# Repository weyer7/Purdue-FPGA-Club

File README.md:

# FPGA Club

Promoting student-led design, verification, and implementation of user-defined hardware.

---

## General Meeting Information
- **Meeting Frequency**: Biweekly  
- **Location**: BHEE 117 (ECE 270 Lab)  
- **Meeting Time**: Thursday at 7:40pm

---

## Subteam Meeting Times
- **Meeting Time**: TBD (determined via when2meet polls in the announcements channel)  
- Members can choose their subteam and participate accordingly.

---

## Labs and Equipment Usage
- **Access**: Students may use the ECE 270 Lab (BHEE 164) at any time outside class hours to work on projects.  
- **Club Equipment**: Located in the club locker (Cabinet 15) at the back of the lab. Equipment use is allowed after attending at least one meeting.

### Lab and Equipment Rules
1. **Authorization Required**: Do not remove FPGA club property or lab equipment from the lab space without authorization.  
2. **No Food/Drinks**: These are not permitted in the ECE 270 Lab.  
3. **Clean and Organize**: Return all equipment to its proper place.  
4. **Respect Others**: Lab usage is a privilege provided by the ECE department.

---

## Project Paths
For **Spring 2025**, the club offers the following two project paths:

### 1. 270 FPGA Development Board
- **Objective**: Design and prototype a new low-cost FPGA board for Purdue’s ECE 270 class.  
- **Tools**: KiCad (for PCB design and layout).  
- **Goal**: Deliver a working prototype by the semester's end.  
- **Support**: Subteam members will receive guidance in learning the tools and debugging/design processes.

### 2. Digital Design Project
- **Objective**: Collaborate in small teams (about 4 members) to create an FPGA project for the **ECE Spark Competition**.  
- **Examples**:
  - A **MIDI synthesizer** that processes music signals to generate sound output for headphones.  
  - A **snake game** where buttons control the speed or direction of the snake.  
- **Project Suggestions Forum**: Members can pitch ideas and form teams based on shared interests.

---

## Getting Started
1. **Join a Project Path**: Choose between the 270 FPGA Development Board or Digital Design Project subteams.  
2. **Participate in Meetings**: Stay updated via the announcements channel.  
3. **Use the Lab**: Ensure you’ve attended at least one meeting before using the lab equipment.

---

## Contact
For questions, feel free to reach out to FPGA Club officers via the [Discord](https://discord.com/invite/DYDBBp7gQk).

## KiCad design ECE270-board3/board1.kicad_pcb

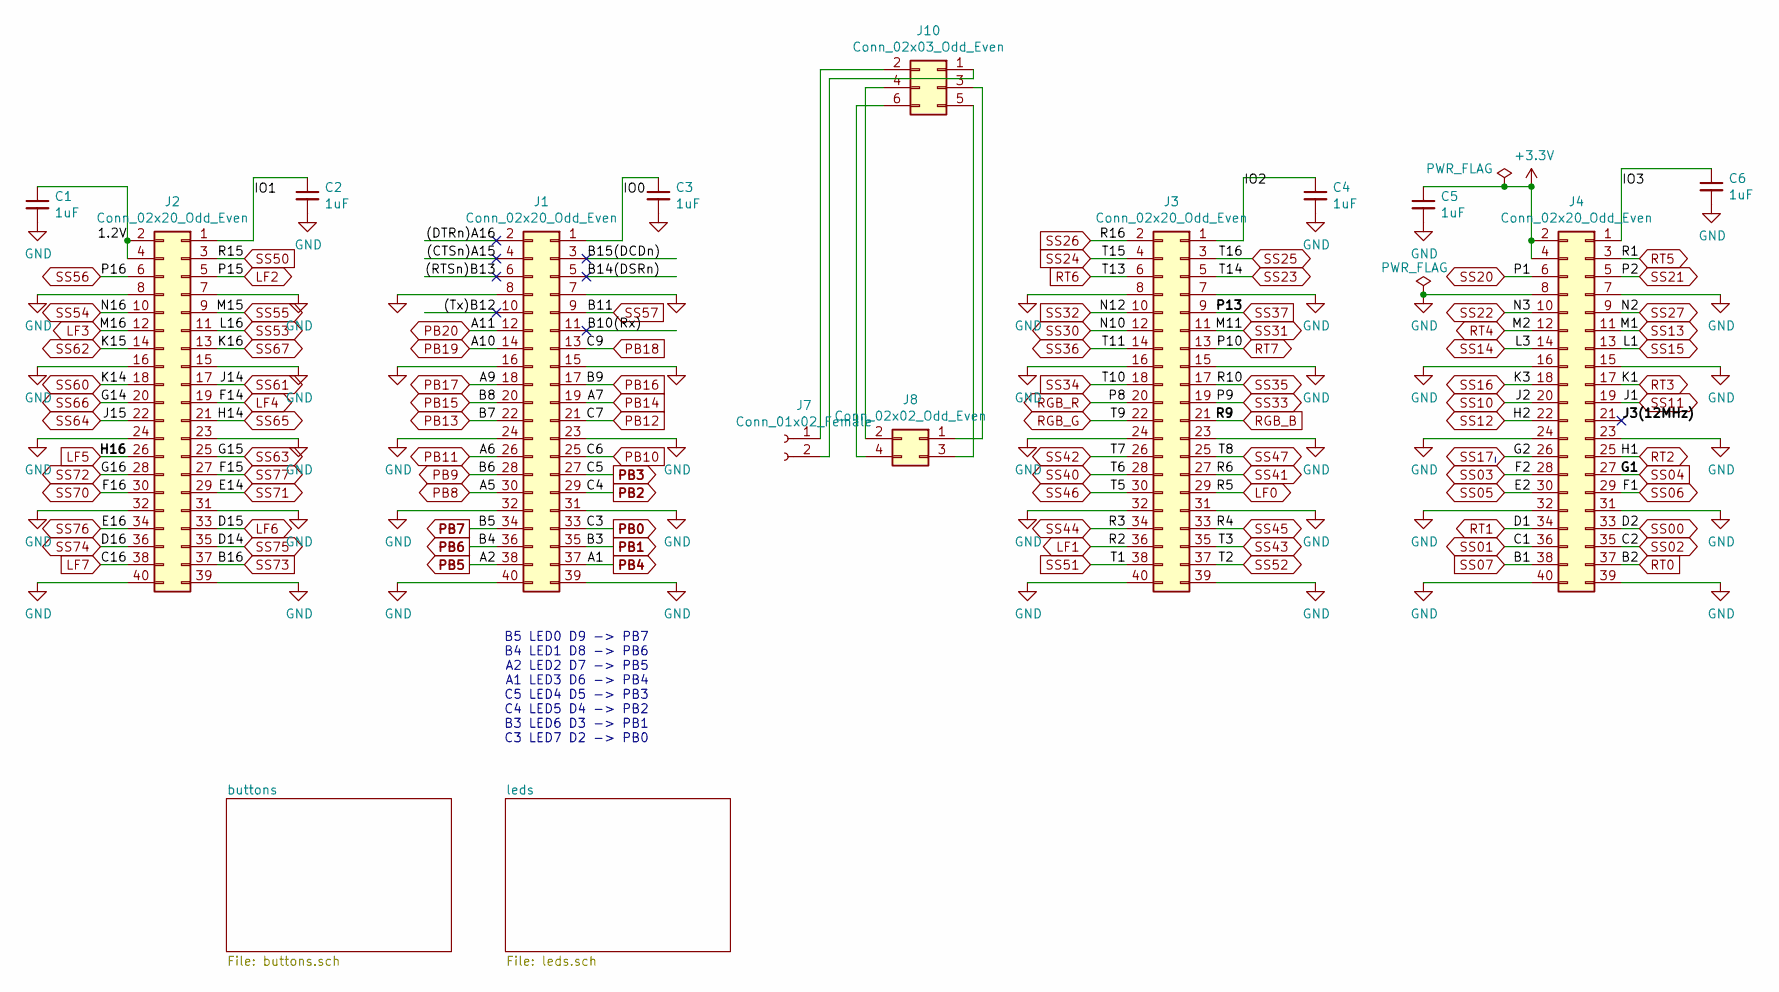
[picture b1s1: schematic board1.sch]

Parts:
C1, C2, C3, C4, C5, C6: 1uF; C_0603_1608Metric
J1, J2, J3, J4: Conn_02x20_Odd_Even; PinHeader_2x20_P2.54mm_Vertical_SMD
J7: Conn_01x02_Female; PinSocket_1x02_P2.54mm_Vertical_SMD_Pin1Left
J8: Conn_02x02_Odd_Even; PinSocket_2x02_P2.54mm_Vertical_SMD
J10: Conn_02x03_Odd_Even; PinHeader_2x03_P2.54mm_Vertical_SMD

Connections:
+3V3: C5.1, J4.2, J4.4; also elsewhere on the board
/1.2V: C1.1, J2.2, J2.4
/(CTSn)A15: J1.4
/(DTRn)A16: J1.2
/(RTSn)B13: J1.6
/(Tx)B12: J1.10
/B10(Rx): J1.11
/B14(DSRn): J1.5
/B15(DCDn): J1.3
/IO0: C3.1, J1.1
/IO1: C2.1, J2.1
/IO2: C4.1, J3.1
/IO3: C6.1, J4.1
/J3(12MHz): J4.21
GND: C1.2, C2.2, C3.2, C4.2, C5.2, C6.2, J1.7, J1.8, J1.15, J1.16, J1.23, J1.24, J1.31, J1.32, J1.39, J1.40, J2.7, J2.8, J2.15, J2.16, J2.23, J2.24, J2.31, J2.32, J2.39, J2.40, J3.7, J3.8, J3.15, J3.16, J3.23, J3.24, J3.31, J3.32, J3.39, J3.40, J4.7, J4.8, J4.15, J4.16, J4.23, J4.24, J4.31, J4.32, J4.39, J4.40; also elsewhere on the board
LF0: J3.29; also elsewhere on the board
LF1: J3.36; also elsewhere on the board
LF2: J2.5; also elsewhere on the board
LF3: J2.12; also elsewhere on the board
LF4: J2.19; also elsewhere on the board
LF5: J2.26; also elsewhere on the board
LF6: J2.33; also elsewhere on the board
LF7: J2.38; also elsewhere on the board
unnamed: J7.2, J10.1
unnamed: J7.1, J10.2
unnamed: J8.1, J10.3
unnamed: J8.2, J10.4
unnamed: J8.3, J10.5
unnamed: J8.4, J10.6
PB0: J1.33; also elsewhere on the board
PB1: J1.35; also elsewhere on the board
PB2: J1.29; also elsewhere on the board
PB3: J1.27; also elsewhere on the board
PB4: J1.37; also elsewhere on the board
PB5: J1.38; also elsewhere on the board
PB6: J1.36; also elsewhere on the board
PB7: J1.34; also elsewhere on the board
PB8: J1.30; also elsewhere on the board
PB9: J1.28; also elsewhere on the board
PB10: J1.25; also elsewhere on the board
PB11: J1.26; also elsewhere on the board
PB12: J1.21; also elsewhere on the board
PB13: J1.22; also elsewhere on the board
PB14: J1.19; also elsewhere on the board
PB15: J1.20; also elsewhere on the board
PB16: J1.17; also elsewhere on the board
PB17: J1.18; also elsewhere on the board
PB18: J1.13; also elsewhere on the board
PB19: J1.14; also elsewhere on the board
PB20: J1.12; also elsewhere on the board
RGB_B: J3.21; also elsewhere on the board
RGB_G: J3.22; also elsewhere on the board
RGB_R: J3.20; also elsewhere on the board
RT0: J4.37; also elsewhere on the board
RT1: J4.34; also elsewhere on the board
RT2: J4.25; also elsewhere on the board
RT3: J4.17; also elsewhere on the board
RT4: J4.12; also elsewhere on the board
RT5: J4.3; also elsewhere on the board
RT6: J3.6; also elsewhere on the board
RT7: J3.13; also elsewhere on the board
SS00: J4.33; also elsewhere on the board
SS01: J4.36; also elsewhere on the board
SS02: J4.35; also elsewhere on the board
SS03: J4.28; also elsewhere on the board
SS04: J4.27; also elsewhere on the board
SS05: J4.30; also elsewhere on the board
SS06: J4.29; also elsewhere on the board
SS07: J4.38; also elsewhere on the board
SS10: J4.20; also elsewhere on the board
SS11: J4.19; also elsewhere on the board
SS12: J4.22; also elsewhere on the board
SS13: J4.11; also elsewhere on the board
SS14: J4.14; also elsewhere on the board
SS15: J4.13; also elsewhere on the board
SS16: J4.18; also elsewhere on the board
SS17: J4.26; also elsewhere on the board
SS20: J4.6; also elsewhere on the board
SS21: J4.5; also elsewhere on the board
SS22: J4.10; also elsewhere on the board
SS23: J3.5; also elsewhere on the board
SS24: J3.4; also elsewhere on the board
SS25: J3.3; also elsewhere on the board
SS26: J3.2; also elsewhere on the board
SS27: J4.9; also elsewhere on the board
SS30: J3.12; also elsewhere on the board
SS31: J3.11; also elsewhere on the board
SS32: J3.10; also elsewhere on the board
SS33: J3.19; also elsewhere on the board
SS34: J3.18; also elsewhere on the board
SS35: J3.17; also elsewhere on the board
SS36: J3.14; also elsewhere on the board
SS37: J3.9; also elsewhere on the board
SS40: J3.28; also elsewhere on the board
SS41: J3.27; also elsewhere on the board
SS42: J3.26; also elsewhere on the board
SS43: J3.35; also elsewhere on the board
SS44: J3.34; also elsewhere on the board
SS45: J3.33; also elsewhere on the board
SS46: J3.30; also elsewhere on the board
SS47: J3.25; also elsewhere on the board
SS50: J2.3; also elsewhere on the board
SS51: J3.38; also elsewhere on the board
SS52: J3.37; also elsewhere on the board
SS53: J2.11; also elsewhere on the board
SS54: J2.10; also elsewhere on the board
SS55: J2.9; also elsewhere on the board
SS56: J2.6; also elsewhere on the board
SS57: J1.9; also elsewhere on the board
SS60: J2.18; also elsewhere on the board
SS61: J2.17; also elsewhere on the board
SS62: J2.14; also elsewhere on the board
SS63: J2.25; also elsewhere on the board
SS64: J2.22; also elsewhere on the board
SS65: J2.21; also elsewhere on the board
SS66: J2.20; also elsewhere on the board
SS67: J2.13; also elsewhere on the board
SS70: J2.30; also elsewhere on the board
SS71: J2.29; also elsewhere on the board
SS72: J2.28; also elsewhere on the board
SS73: J2.37; also elsewhere on the board
SS74: J2.36; also elsewhere on the board
SS75: J2.35; also elsewhere on the board
SS76: J2.34; also elsewhere on the board
SS77: J2.27; also elsewhere on the board

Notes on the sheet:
B5 LED0 D9 -> PB7 B4 LED1 D8 -> PB6 A2 LED2 D7 -> PB5 A1 LED3 D6 -> PB4 C5 LED4 D5 -> PB3 C4 LED5 D4 -> PB2 B3 LED6 D3 -> PB1 C3 LED7 D2 -> PB0

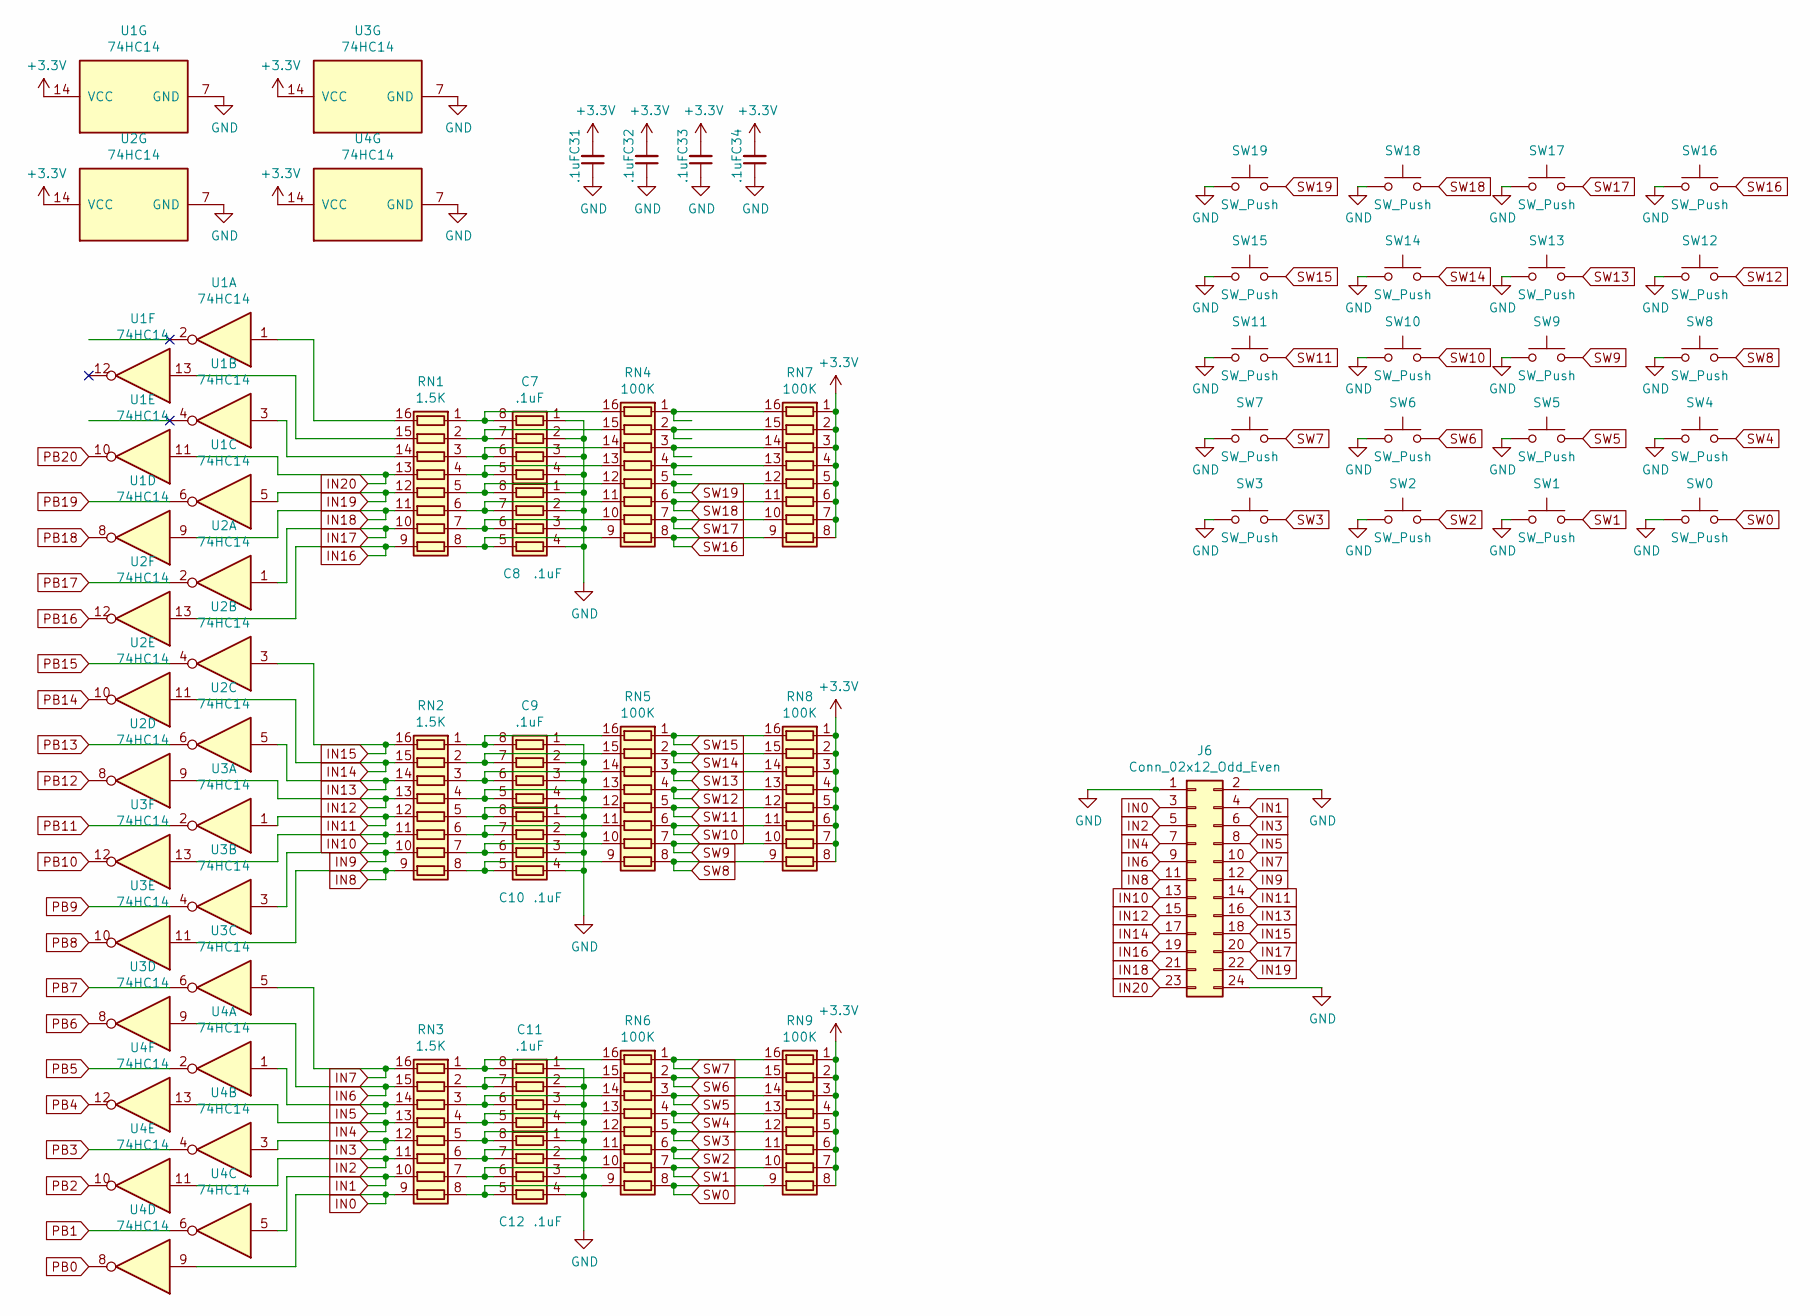
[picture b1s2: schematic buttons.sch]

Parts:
C7, C8, C9, C10, C11, C12: .1uF; R_Array_Convex_4x0612
C31, C32, C33, C34: .1uF; C_0603_1608Metric
J6: Conn_02x12_Odd_Even; Samtec_HLE-112-02-xxx-DV_2x12_P2.54mm_Horizontal
RN1, RN2, RN3: 1.5K; SOIC-16_3.9x9.9mm_P1.27mm
RN4, RN5, RN6, RN7, RN8, RN9: 100K; SOIC-16_3.9x9.9mm_P1.27mm
SW0, SW1, SW2, SW3, SW4, SW5, SW6, SW7, SW8, SW9, SW10, SW11, SW12, SW13, SW14, SW15, SW16, SW17, SW18, SW19: SW_Push; SW_SPST_B3FS-4052P
U1, U2, U3, U4: 74HC14; SOIC-14_3.9x8.7mm_P1.27mm

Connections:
+3V3: C31.2, C32.2, C33.2, C34.2, RN7.1 (R1.1), RN7.2 (R2.1), RN7.3 (R3.1), RN7.4 (R4.1), RN7.5 (R5.1), RN7.6 (R6.1), RN7.7 (R7.1), RN7.8 (R8.1), RN8.1 (R1.1), RN8.2 (R2.1), RN8.3 (R3.1), RN8.4 (R4.1), RN8.5 (R5.1), RN8.6 (R6.1), RN8.7 (R7.1), RN8.8 (R8.1), RN9.1 (R1.1), RN9.2 (R2.1), RN9.3 (R3.1), RN9.4 (R4.1), RN9.5 (R5.1), RN9.6 (R6.1), RN9.7 (R7.1), RN9.8 (R8.1), U1.14 (VCC), U2.14 (VCC), U3.14 (VCC), U4.14 (VCC); also elsewhere on the board
GND: C7.1 (R1.1), C7.2 (R2.1), C7.3 (R3.1), C7.4 (R4.1), C8.1 (R1.1), C8.2 (R2.1), C8.3 (R3.1), C8.4 (R4.1), C9.1 (R1.1), C9.2 (R2.1), C9.3 (R3.1), C9.4 (R4.1), C10.1 (R1.1), C10.2 (R2.1), C10.3 (R3.1), C10.4 (R4.1), C11.1 (R1.1), C11.2 (R2.1), C11.3 (R3.1), C11.4 (R4.1), C12.1 (R1.1), C12.2 (R2.1), C12.3 (R3.1), C12.4 (R4.1), C31.1, C32.1, C33.1, C34.1, J6.1, J6.2, J6.24, SW0.1, SW1.1, SW2.1, SW3.1, SW4.1, SW5.1, SW6.1, SW7.1, SW8.1, SW9.1, SW10.1, SW11.1, SW12.1, SW13.1, SW14.1, SW15.1, SW16.1, SW17.1, SW18.1, SW19.1, U1.7 (GND), U2.7 (GND), U3.7 (GND), U4.7 (GND); also elsewhere on the board
IN0: J6.3, RN3.9 (R8.2), U4.9
IN1: J6.4, RN3.10 (R7.2), U4.5
IN2: J6.5, RN3.11 (R6.2), U4.11
IN3: J6.6, RN3.12 (R5.2), U4.3
IN4: J6.7, RN3.13 (R4.2), U4.13
IN5: J6.8, RN3.14 (R3.2), U4.1
IN6: J6.9, RN3.15 (R2.2), U3.9
IN7: J6.10, RN3.16 (R1.2), U3.5
IN8: J6.11, RN2.9 (R8.2), U3.11
IN9: J6.12, RN2.10 (R7.2), U3.3
IN10: J6.13, RN2.11 (R6.2), U3.13
IN11: J6.14, RN2.12 (R5.2), U3.1
IN12: J6.15, RN2.13 (R4.2), U2.9
IN13: J6.16, RN2.14 (R3.2), U2.5
IN14: J6.17, RN2.15 (R2.2), U2.11
IN15: J6.18, RN2.16 (R1.2), U2.3
IN16: J6.19, RN1.9 (R8.2), U2.13
IN17: J6.20, RN1.10 (R7.2), U2.1
IN18: J6.21, RN1.11 (R6.2), U1.9
IN19: J6.22, RN1.12 (R5.2), U1.5
IN20: J6.23, RN1.13 (R4.2), U1.11
unnamed: C7.5 (R4.2), RN1.4 (R4.1), RN4.13 (R4.2)
unnamed: C7.6 (R3.2), RN1.3 (R3.1), RN4.14 (R3.2)
unnamed: C7.7 (R2.2), RN1.2 (R2.1), RN4.15 (R2.2)
unnamed: C7.8 (R1.2), RN1.1 (R1.1), RN4.16 (R1.2)
unnamed: C8.5 (R4.2), RN1.8 (R8.1), RN4.9 (R8.2)
unnamed: C8.6 (R3.2), RN1.7 (R7.1), RN4.10 (R7.2)
unnamed: C8.7 (R2.2), RN1.6 (R6.1), RN4.11 (R6.2)
unnamed: C8.8 (R1.2), RN1.5 (R5.1), RN4.12 (R5.2)
unnamed: C9.5 (R4.2), RN2.4 (R4.1), RN5.13 (R4.2)
unnamed: C9.6 (R3.2), RN2.3 (R3.1), RN5.14 (R3.2)
unnamed: C9.7 (R2.2), RN2.2 (R2.1), RN5.15 (R2.2)
unnamed: C9.8 (R1.2), RN2.1 (R1.1), RN5.16 (R1.2)
unnamed: C10.5 (R4.2), RN2.8 (R8.1), RN5.9 (R8.2)
unnamed: C10.6 (R3.2), RN2.7 (R7.1), RN5.10 (R7.2)
unnamed: C10.7 (R2.2), RN2.6 (R6.1), RN5.11 (R6.2)
unnamed: C10.8 (R1.2), RN2.5 (R5.1), RN5.12 (R5.2)
unnamed: C11.5 (R4.2), RN3.4 (R4.1), RN6.13 (R4.2)
unnamed: C11.6 (R3.2), RN3.3 (R3.1), RN6.14 (R3.2)
unnamed: C11.7 (R2.2), RN3.2 (R2.1), RN6.15 (R2.2)
unnamed: C11.8 (R1.2), RN3.1 (R1.1), RN6.16 (R1.2)
unnamed: C12.5 (R4.2), RN3.8 (R8.1), RN6.9 (R8.2)
unnamed: C12.6 (R3.2), RN3.7 (R7.1), RN6.10 (R7.2)
unnamed: C12.7 (R2.2), RN3.6 (R6.1), RN6.11 (R6.2)
unnamed: C12.8 (R1.2), RN3.5 (R5.1), RN6.12 (R5.2)
unnamed: RN1.14 (R3.2), U1.3
unnamed: RN1.15 (R2.2), U1.13
unnamed: RN1.16 (R1.2), U1.1
unnamed: RN4.1 (R1.1), RN7.16 (R1.2)
unnamed: RN4.2 (R2.1), RN7.15 (R2.2)
unnamed: RN4.3 (R3.1), RN7.14 (R3.2)
unnamed: RN4.4 (R4.1), RN7.13 (R4.2)
PB0: U4.8; also elsewhere on the board
PB1: U4.6; also elsewhere on the board
PB2: U4.10; also elsewhere on the board
PB3: U4.4; also elsewhere on the board
PB4: U4.12; also elsewhere on the board
PB5: U4.2; also elsewhere on the board
PB6: U3.8; also elsewhere on the board
PB7: U3.6; also elsewhere on the board
PB8: U3.10; also elsewhere on the board
PB9: U3.4; also elsewhere on the board
PB10: U3.12; also elsewhere on the board
PB11: U3.2; also elsewhere on the board
PB12: U2.8; also elsewhere on the board
PB13: U2.6; also elsewhere on the board
PB14: U2.10; also elsewhere on the board
PB15: U2.4; also elsewhere on the board
PB16: U2.12; also elsewhere on the board
PB17: U2.2; also elsewhere on the board
PB18: U1.8; also elsewhere on the board
PB19: U1.6; also elsewhere on the board
PB20: U1.10; also elsewhere on the board
SW0: RN6.8 (R8.1), RN9.9 (R8.2), SW0.2
SW1: RN6.7 (R7.1), RN9.10 (R7.2), SW1.2
SW2: RN6.6 (R6.1), RN9.11 (R6.2), SW2.2
SW3: RN6.5 (R5.1), RN9.12 (R5.2), SW3.2
SW4: RN6.4 (R4.1), RN9.13 (R4.2), SW4.2
SW5: RN6.3 (R3.1), RN9.14 (R3.2), SW5.2
SW6: RN6.2 (R2.1), RN9.15 (R2.2), SW6.2
SW7: RN6.1 (R1.1), RN9.16 (R1.2), SW7.2
SW8: RN5.8 (R8.1), RN8.9 (R8.2), SW8.2
SW9: RN5.7 (R7.1), RN8.10 (R7.2), SW9.2
SW10: RN5.6 (R6.1), RN8.11 (R6.2), SW10.2
SW11: RN5.5 (R5.1), RN8.12 (R5.2), SW11.2
SW12: RN5.4 (R4.1), RN8.13 (R4.2), SW12.2
SW13: RN5.3 (R3.1), RN8.14 (R3.2), SW13.2
SW14: RN5.2 (R2.1), RN8.15 (R2.2), SW14.2
SW15: RN5.1 (R1.1), RN8.16 (R1.2), SW15.2
SW16: RN4.8 (R8.1), RN7.9 (R8.2), SW16.2
SW17: RN4.7 (R7.1), RN7.10 (R7.2), SW17.2
SW18: RN4.6 (R6.1), RN7.11 (R6.2), SW18.2
SW19: RN4.5 (R5.1), RN7.12 (R5.2), SW19.2

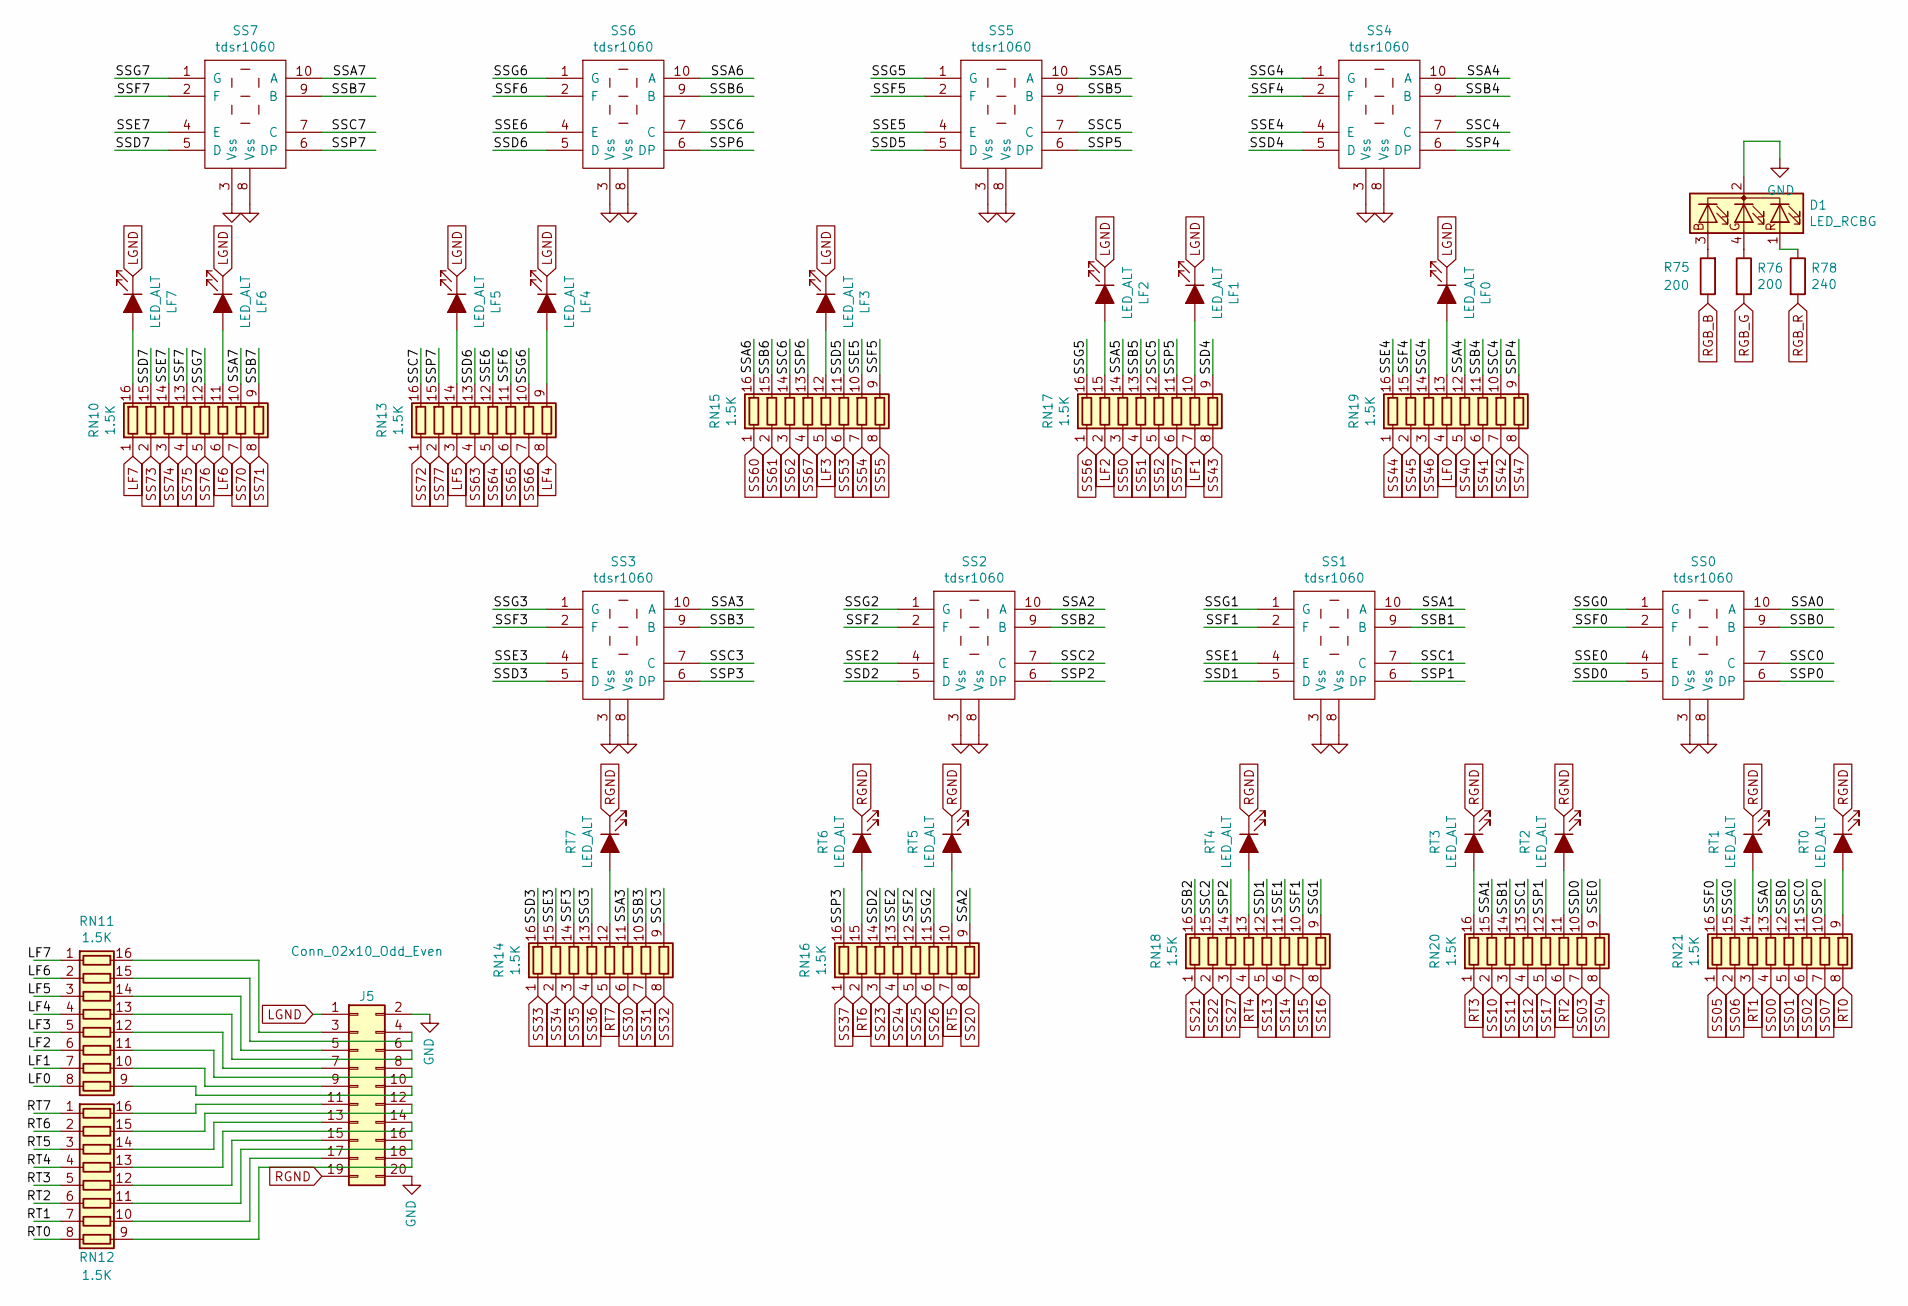
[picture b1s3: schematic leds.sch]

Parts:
D1: LED_RCBG; LED_D5.0mm-4_RGB
J5: Conn_02x10_Odd_Even; Samtec_HLE-110-02-xxx-DV_2x10_P2.54mm_Horizontal
LF0, LF1, LF2, LF3, LF4, LF5, LF6, LF7: LED_ALT; LED_D3.0mm
R75, R76: 200; R_0805_2012Metric
R78: 240; R_0805_2012Metric
RN10, RN11, RN12, RN13, RN14, RN15, RN16, RN17, RN18, RN19, RN20, RN21: 1.5K; SOIC-16_3.9x9.9mm_P1.27mm
RT0, RT1, RT2, RT3, RT4, RT5, RT6, RT7: LED_ALT; LED_D3.0mm
SS0, SS1, SS2, SS3, SS4, SS5, SS6, SS7: tdsr1060; DIP-10_W7.62mm

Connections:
/leds/SSA0: RN21.13 (R4.2), SS0.10 (A)
/leds/SSA1: RN20.15 (R2.2), SS1.10 (A)
/leds/SSA2: RN16.9 (R8.2), SS2.10 (A)
/leds/SSA3: RN14.11 (R6.2), SS3.10 (A)
/leds/SSA4: RN19.12 (R5.2), SS4.10 (A)
/leds/SSA5: RN17.14 (R3.2), SS5.10 (A)
/leds/SSA6: RN15.16 (R1.2), SS6.10 (A)
/leds/SSA7: RN10.10 (R7.2), SS7.10 (A)
/leds/SSB0: RN21.12 (R5.2), SS0.9 (B)
/leds/SSB1: RN20.14 (R3.2), SS1.9 (B)
/leds/SSB2: RN18.16 (R1.2), SS2.9 (B)
/leds/SSB3: RN14.10 (R7.2), SS3.9 (B)
/leds/SSB4: RN19.11 (R6.2), SS4.9 (B)
/leds/SSB5: RN17.13 (R4.2), SS5.9 (B)
/leds/SSB6: RN15.15 (R2.2), SS6.9 (B)
/leds/SSB7: RN10.9 (R8.2), SS7.9 (B)
/leds/SSC0: RN21.11 (R6.2), SS0.7 (C)
/leds/SSC1: RN20.13 (R4.2), SS1.7 (C)
/leds/SSC2: RN18.15 (R2.2), SS2.7 (C)
/leds/SSC3: RN14.9 (R8.2), SS3.7 (C)
/leds/SSC4: RN19.10 (R7.2), SS4.7 (C)
/leds/SSC5: RN17.12 (R5.2), SS5.7 (C)
/leds/SSC6: RN15.14 (R3.2), SS6.7 (C)
/leds/SSC7: RN13.16 (R1.2), SS7.7 (C)
/leds/SSD0: RN20.10 (R7.2), SS0.5 (D)
/leds/SSD1: RN18.12 (R5.2), SS1.5 (D)
/leds/SSD2: RN16.14 (R3.2), SS2.5 (D)
/leds/SSD3: RN14.16 (R1.2), SS3.5 (D)
/leds/SSD4: RN17.9 (R8.2), SS4.5 (D)
/leds/SSD5: RN15.11 (R6.2), SS5.5 (D)
/leds/SSD6: RN13.13 (R4.2), SS6.5 (D)
/leds/SSD7: RN10.15 (R2.2), SS7.5 (D)
/leds/SSE0: RN20.9 (R8.2), SS0.4 (E)
/leds/SSE1: RN18.11 (R6.2), SS1.4 (E)
/leds/SSE2: RN16.13 (R4.2), SS2.4 (E)
/leds/SSE3: RN14.15 (R2.2), SS3.4 (E)
/leds/SSE4: RN19.16 (R1.2), SS4.4 (E)
/leds/SSE5: RN15.10 (R7.2), SS5.4 (E)
/leds/SSE6: RN13.12 (R5.2), SS6.4 (E)
/leds/SSE7: RN10.14 (R3.2), SS7.4 (E)
/leds/SSF0: RN21.16 (R1.2), SS0.2 (F)
/leds/SSF1: RN18.10 (R7.2), SS1.2 (F)
/leds/SSF2: RN16.12 (R5.2), SS2.2 (F)
/leds/SSF3: RN14.14 (R3.2), SS3.2 (F)
/leds/SSF4: RN19.15 (R2.2), SS4.2 (F)
/leds/SSF5: RN15.9 (R8.2), SS5.2 (F)
/leds/SSF6: RN13.11 (R6.2), SS6.2 (F)
/leds/SSF7: RN10.13 (R4.2), SS7.2 (F)
/leds/SSG0: RN21.15 (R2.2), SS0.1 (G)
/leds/SSG1: RN18.9 (R8.2), SS1.1 (G)
/leds/SSG2: RN16.11 (R6.2), SS2.1 (G)
/leds/SSG3: RN14.13 (R4.2), SS3.1 (G)
/leds/SSG4: RN19.14 (R3.2), SS4.1 (G)
/leds/SSG5: RN17.16 (R1.2), SS5.1 (G)
/leds/SSG6: RN13.10 (R7.2), SS6.1 (G)
/leds/SSG7: RN10.12 (R5.2), SS7.1 (G)
/leds/SSP0: RN21.10 (R7.2), SS0.6 (DP)
/leds/SSP1: RN20.12 (R5.2), SS1.6 (DP)
/leds/SSP2: RN18.14 (R3.2), SS2.6 (DP)
/leds/SSP3: RN16.16 (R1.2), SS3.6 (DP)
/leds/SSP4: RN19.9 (R8.2), SS4.6 (DP)
/leds/SSP5: RN17.11 (R6.2), SS5.6 (DP)
/leds/SSP6: RN15.13 (R4.2), SS6.6 (DP)
/leds/SSP7: RN13.15 (R2.2), SS7.6 (DP)
GND: D1.2 (K), J5.2, J5.20, SS0.3 (Vss), SS0.8 (Vss), SS1.3 (Vss), SS1.8 (Vss), SS2.3 (Vss), SS2.8 (Vss), SS3.3 (Vss), SS3.8 (Vss), SS4.3 (Vss), SS4.8 (Vss), SS5.3 (Vss), SS5.8 (Vss), SS6.3 (Vss), SS6.8 (Vss), SS7.3 (Vss), SS7.8 (Vss); also elsewhere on the board
LF0: RN11.8 (R8.1), RN19.4 (R4.1); also elsewhere on the board
LF1: RN11.7 (R7.1), RN17.7 (R7.1); also elsewhere on the board
LF2: RN11.6 (R6.1), RN17.2 (R2.1); also elsewhere on the board
LF3: RN11.5 (R5.1), RN15.5 (R5.1); also elsewhere on the board
LF4: RN11.4 (R4.1), RN13.8 (R8.1); also elsewhere on the board
LF5: RN11.3 (R3.1), RN13.3 (R3.1); also elsewhere on the board
LF6: RN10.6 (R6.1), RN11.2 (R2.1); also elsewhere on the board
LF7: RN10.1 (R1.1), RN11.1 (R1.1); also elsewhere on the board
LGND: J5.1, LF0.1 (K), LF1.1 (K), LF2.1 (K), LF3.1 (K), LF4.1 (K), LF5.1 (K), LF6.1 (K), LF7.1 (K)
unnamed: D1.1 (RA), R78.1
unnamed: D1.3 (BA), R75.2
unnamed: D1.4 (GA), R76.1
unnamed: J5.3, RN11.16 (R1.2)
unnamed: J5.4, RN11.15 (R2.2)
unnamed: J5.5, RN11.14 (R3.2)
unnamed: J5.6, RN11.13 (R4.2)
unnamed: J5.7, RN11.12 (R5.2)
unnamed: J5.8, RN11.11 (R6.2)
unnamed: J5.9, RN11.10 (R7.2)
unnamed: J5.10, RN11.9 (R8.2)
unnamed: J5.11, RN12.16 (R1.2)
unnamed: J5.12, RN12.15 (R2.2)
unnamed: J5.13, RN12.14 (R3.2)
unnamed: J5.14, RN12.13 (R4.2)
unnamed: J5.15, RN12.12 (R5.2)
unnamed: J5.16, RN12.11 (R6.2)
unnamed: J5.17, RN12.10 (R7.2)
unnamed: J5.18, RN12.9 (R8.2)
unnamed: LF0.2 (A), RN19.13 (R4.2)
unnamed: LF1.2 (A), RN17.10 (R7.2)
unnamed: LF2.2 (A), RN17.15 (R2.2)
unnamed: LF3.2 (A), RN15.12 (R5.2)
unnamed: LF4.2 (A), RN13.9 (R8.2)
unnamed: LF5.2 (A), RN13.14 (R3.2)
unnamed: LF6.2 (A), RN10.11 (R6.2)
unnamed: LF7.2 (A), RN10.16 (R1.2)
unnamed: RN14.12 (R5.2), RT7.2 (A)
unnamed: RN16.10 (R7.2), RT5.2 (A)
unnamed: RN16.15 (R2.2), RT6.2 (A)
unnamed: RN18.13 (R4.2), RT4.2 (A)
unnamed: RN20.11 (R6.2), RT2.2 (A)
unnamed: RN20.16 (R1.2), RT3.2 (A)
unnamed: RN21.9 (R8.2), RT0.2 (A)
unnamed: RN21.14 (R3.2), RT1.2 (A)
RGB_B: R75.1; also elsewhere on the board
RGB_G: R76.2; also elsewhere on the board
RGB_R: R78.2; also elsewhere on the board
RGND: J5.19, RT0.1 (K), RT1.1 (K), RT2.1 (K), RT3.1 (K), RT4.1 (K), RT5.1 (K), RT6.1 (K), RT7.1 (K)
RT0: RN12.8 (R8.1), RN21.8 (R8.1); also elsewhere on the board
RT1: RN12.7 (R7.1), RN21.3 (R3.1); also elsewhere on the board
RT2: RN12.6 (R6.1), RN20.6 (R6.1); also elsewhere on the board
RT3: RN12.5 (R5.1), RN20.1 (R1.1); also elsewhere on the board
RT4: RN12.4 (R4.1), RN18.4 (R4.1); also elsewhere on the board
RT5: RN12.3 (R3.1), RN16.7 (R7.1); also elsewhere on the board
RT6: RN12.2 (R2.1), RN16.2 (R2.1); also elsewhere on the board
RT7: RN12.1 (R1.1), RN14.5 (R5.1); also elsewhere on the board
SS00: RN21.4 (R4.1); also elsewhere on the board
SS01: RN21.5 (R5.1); also elsewhere on the board
SS02: RN21.6 (R6.1); also elsewhere on the board
SS03: RN20.7 (R7.1); also elsewhere on the board
SS04: RN20.8 (R8.1); also elsewhere on the board
SS05: RN21.1 (R1.1); also elsewhere on the board
SS06: RN21.2 (R2.1); also elsewhere on the board
SS07: RN21.7 (R7.1); also elsewhere on the board
SS10: RN20.2 (R2.1); also elsewhere on the board
SS11: RN20.3 (R3.1); also elsewhere on the board
SS12: RN20.4 (R4.1); also elsewhere on the board
SS13: RN18.5 (R5.1); also elsewhere on the board
SS14: RN18.6 (R6.1); also elsewhere on the board
SS15: RN18.7 (R7.1); also elsewhere on the board
SS16: RN18.8 (R8.1); also elsewhere on the board
SS17: RN20.5 (R5.1); also elsewhere on the board
SS20: RN16.8 (R8.1); also elsewhere on the board
SS21: RN18.1 (R1.1); also elsewhere on the board
SS22: RN18.2 (R2.1); also elsewhere on the board
SS23: RN16.3 (R3.1); also elsewhere on the board
SS24: RN16.4 (R4.1); also elsewhere on the board
SS25: RN16.5 (R5.1); also elsewhere on the board
SS26: RN16.6 (R6.1); also elsewhere on the board
SS27: RN18.3 (R3.1); also elsewhere on the board
SS30: RN14.6 (R6.1); also elsewhere on the board
SS31: RN14.7 (R7.1); also elsewhere on the board
SS32: RN14.8 (R8.1); also elsewhere on the board
SS33: RN14.1 (R1.1); also elsewhere on the board
SS34: RN14.2 (R2.1); also elsewhere on the board
SS35: RN14.3 (R3.1); also elsewhere on the board
SS36: RN14.4 (R4.1); also elsewhere on the board
SS37: RN16.1 (R1.1); also elsewhere on the board
SS40: RN19.5 (R5.1); also elsewhere on the board
SS41: RN19.6 (R6.1); also elsewhere on the board
SS42: RN19.7 (R7.1); also elsewhere on the board
SS43: RN17.8 (R8.1); also elsewhere on the board
SS44: RN19.1 (R1.1); also elsewhere on the board
SS45: RN19.2 (R2.1); also elsewhere on the board
SS46: RN19.3 (R3.1); also elsewhere on the board
SS47: RN19.8 (R8.1); also elsewhere on the board
SS50: RN17.3 (R3.1); also elsewhere on the board
SS51: RN17.4 (R4.1); also elsewhere on the board
SS52: RN17.5 (R5.1); also elsewhere on the board
SS53: RN15.6 (R6.1); also elsewhere on the board
SS54: RN15.7 (R7.1); also elsewhere on the board
SS55: RN15.8 (R8.1); also elsewhere on the board
SS56: RN17.1 (R1.1); also elsewhere on the board
SS57: RN17.6 (R6.1); also elsewhere on the board
SS60: RN15.1 (R1.1); also elsewhere on the board
SS61: RN15.2 (R2.1); also elsewhere on the board
SS62: RN15.3 (R3.1); also elsewhere on the board
SS63: RN13.4 (R4.1); also elsewhere on the board
SS64: RN13.5 (R5.1); also elsewhere on the board
SS65: RN13.6 (R6.1); also elsewhere on the board
SS66: RN13.7 (R7.1); also elsewhere on the board
SS67: RN15.4 (R4.1); also elsewhere on the board
SS70: RN10.7 (R7.1); also elsewhere on the board
SS71: RN10.8 (R8.1); also elsewhere on the board
SS72: RN13.1 (R1.1); also elsewhere on the board
SS73: RN10.2 (R2.1); also elsewhere on the board
SS74: RN10.3 (R3.1); also elsewhere on the board
SS75: RN10.4 (R4.1); also elsewhere on the board
SS76: RN10.5 (R5.1); also elsewhere on the board
SS77: RN13.2 (R2.1); also elsewhere on the board

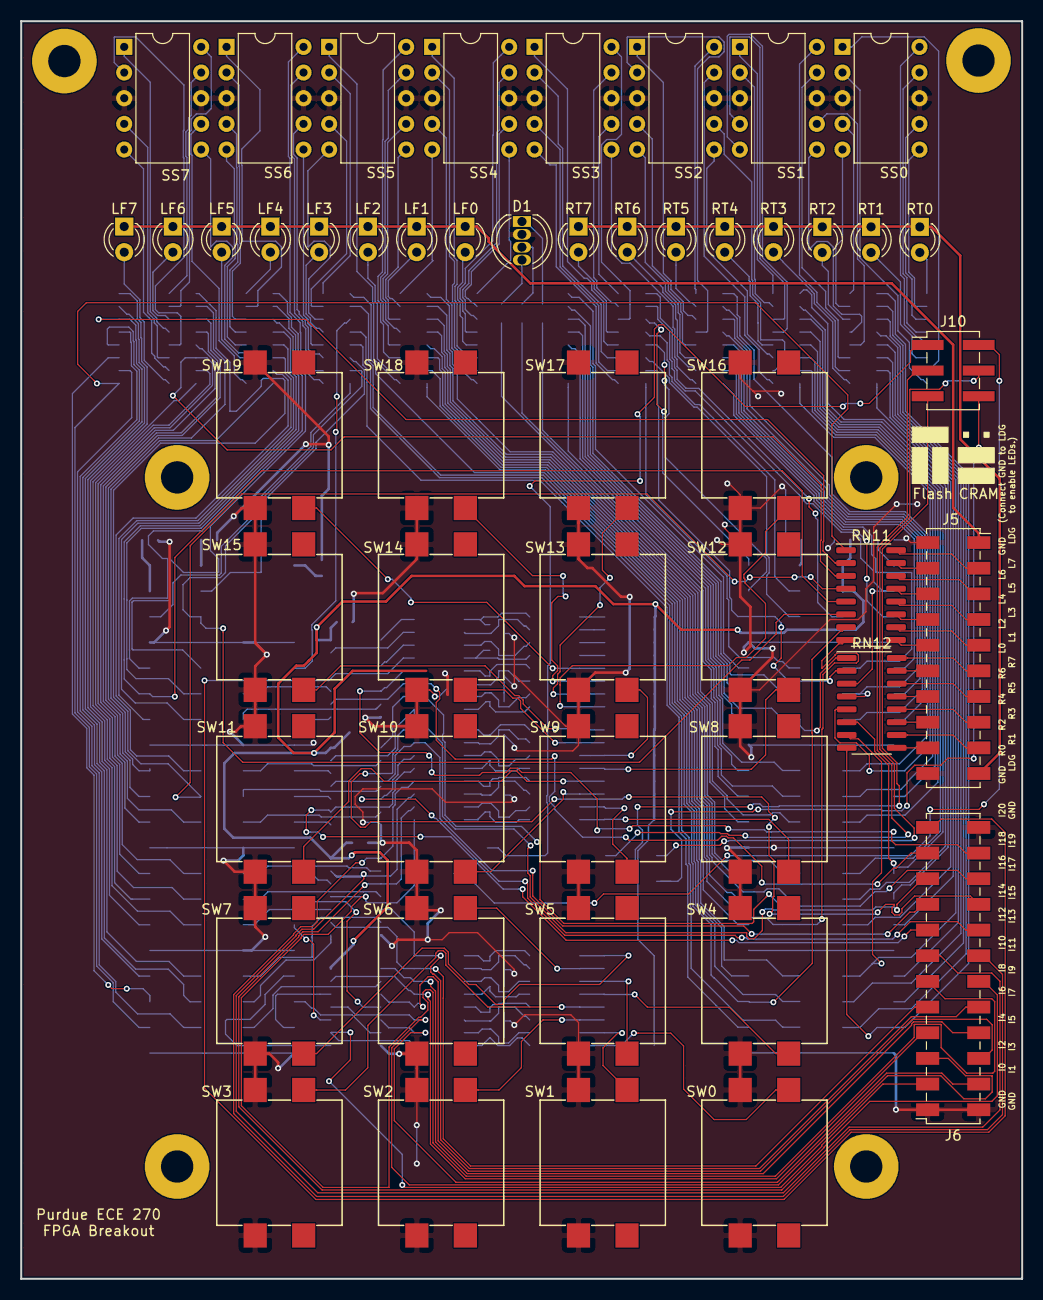
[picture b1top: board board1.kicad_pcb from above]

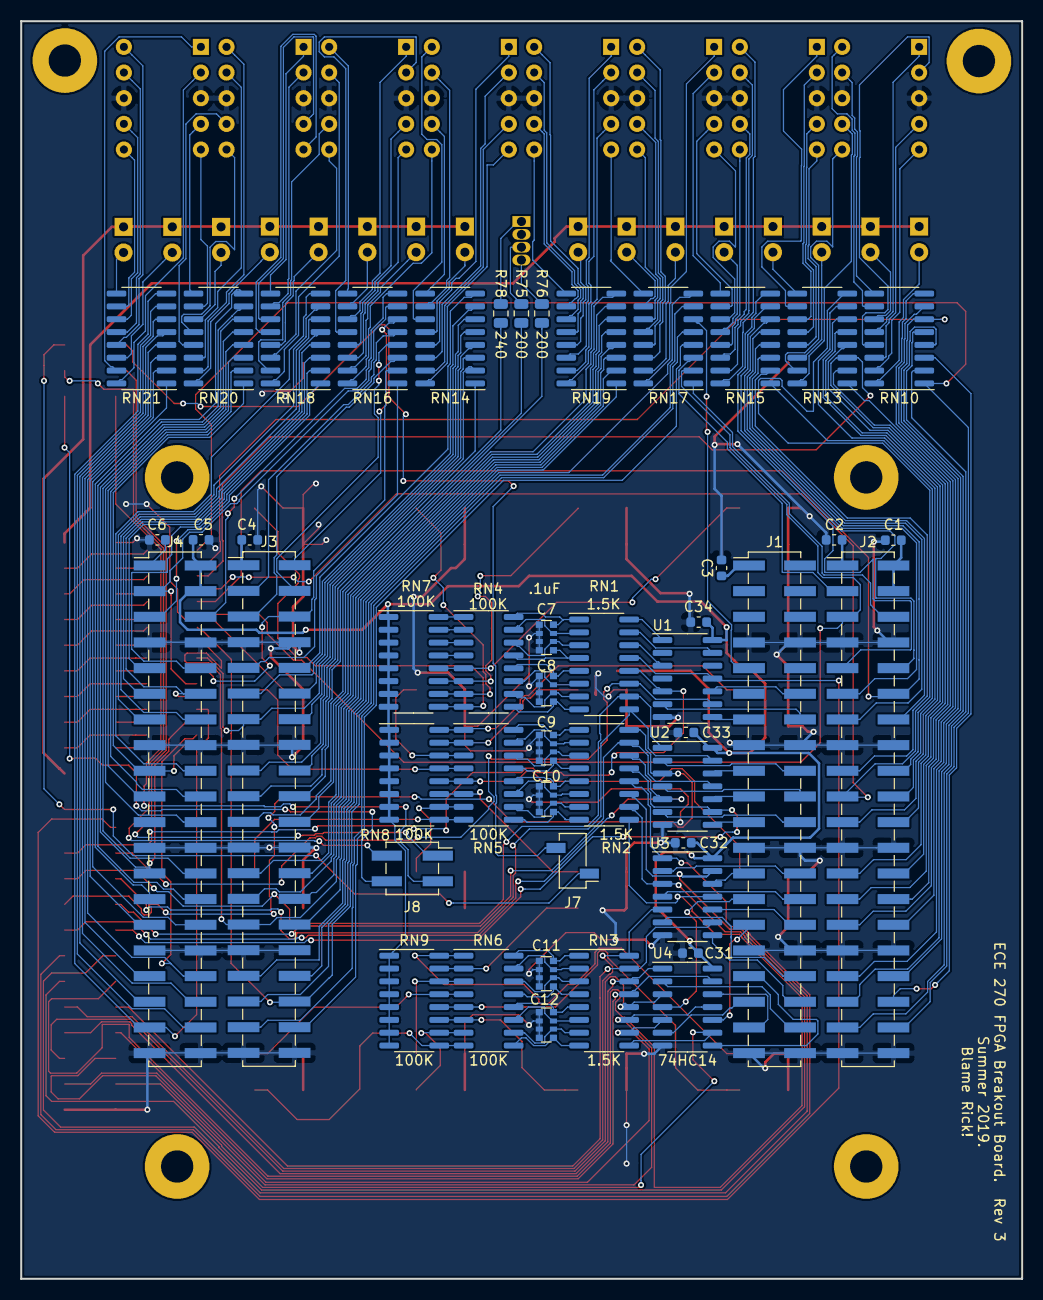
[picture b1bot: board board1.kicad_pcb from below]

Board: 2 copper layers, 99.1 x 124.5 mm, 98 parts (48 on the bottom side), 290 nets.

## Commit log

2025-01-28 Initial Guides
2025-01-28 Rename resources.md to helpful-resources.md
2025-02-01 docs: md format
2025-02-11 docs: add 270-lab-fpga.md
